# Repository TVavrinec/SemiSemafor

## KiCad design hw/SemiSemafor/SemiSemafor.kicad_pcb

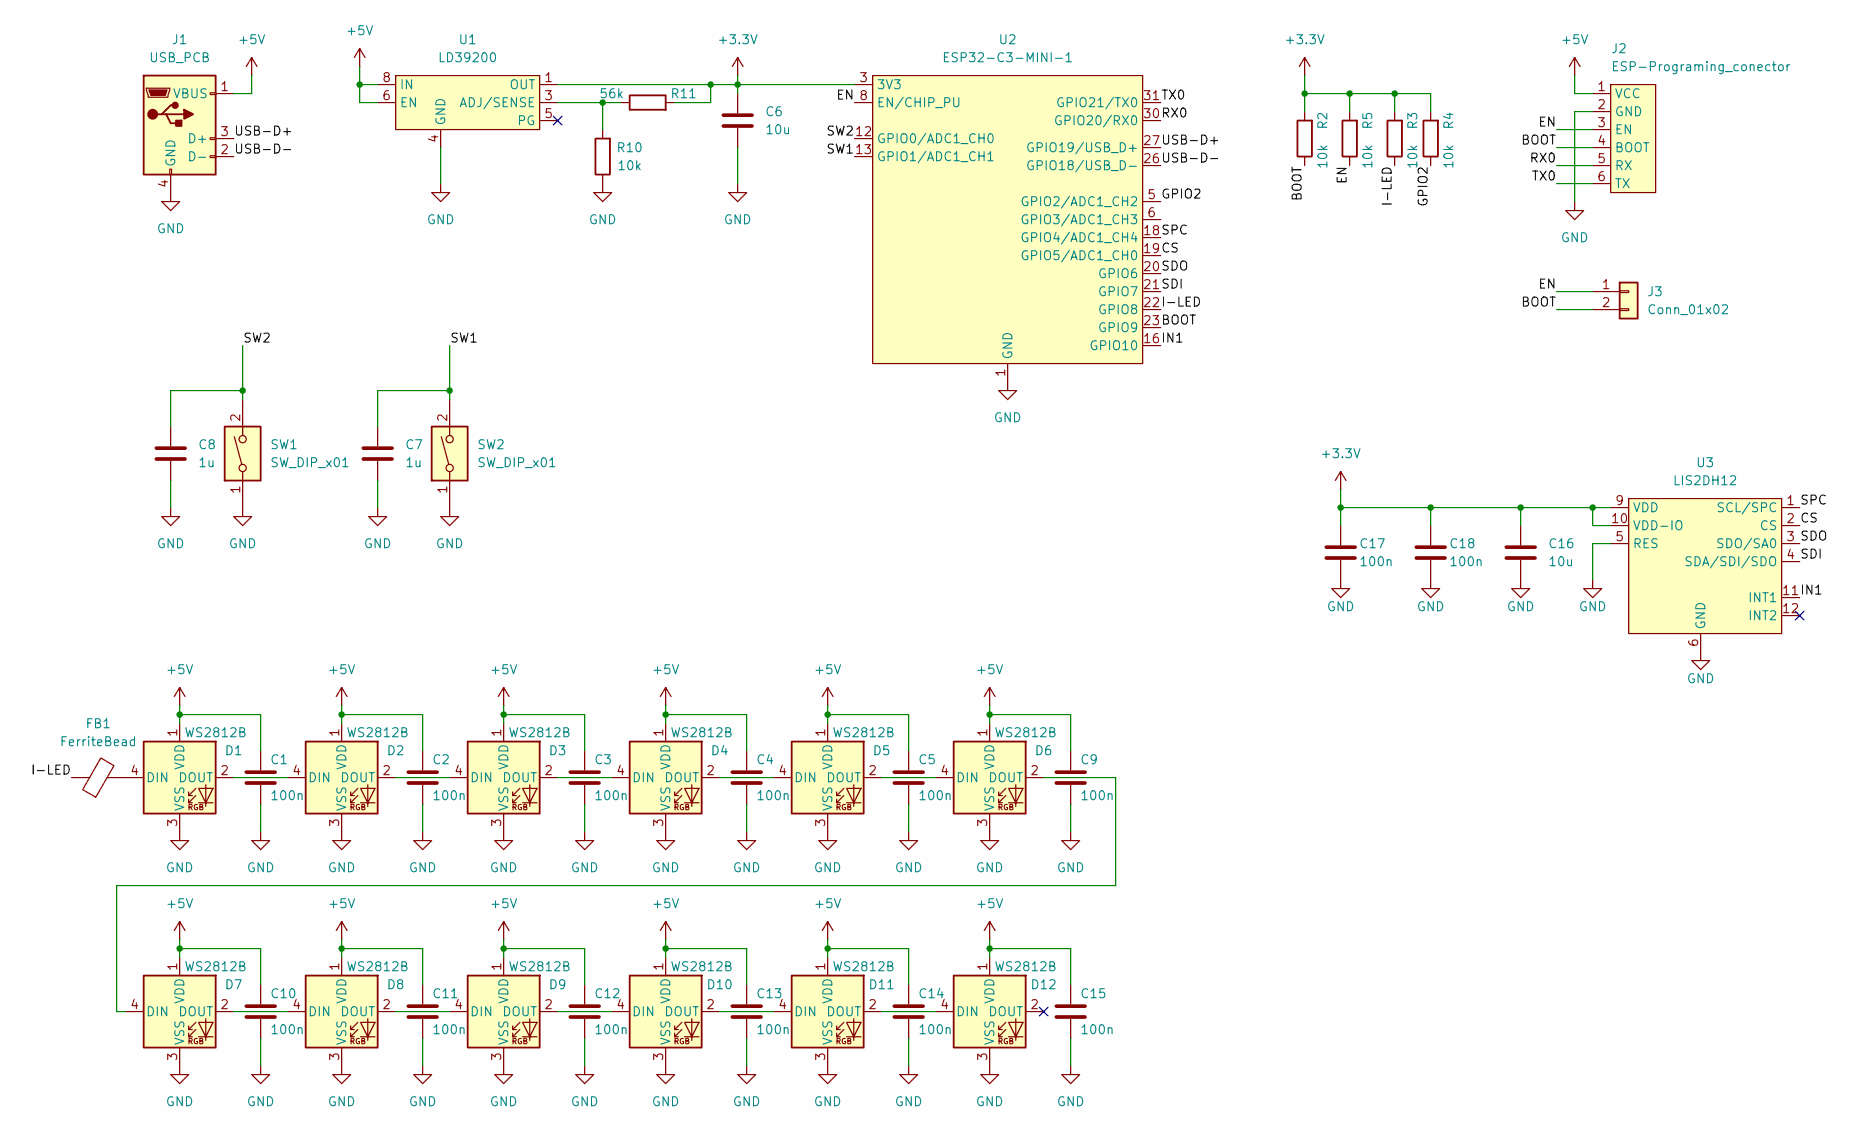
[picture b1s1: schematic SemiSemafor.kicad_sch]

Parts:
C1, C2, C3, C4, C5, C9, C10, C11, C12, C13, C14, C15: 100n; C_0603_1608Metric; LCSC C14663
C6, C16: 10u; C_0603_1608Metric; LCSC C19702
C7, C8: 1u; C_0402_1005Metric; LCSC C52923
C17, C18: 100n; C_0402_1005Metric; LCSC C1525
D1, D2, D3, D4, D5, D6, D7, D8, D9, D10, D11, D12: WS2812B; LED_WS2812B_PLCC4_5.0x5.0mm_P3.2mm; LCSC C2920042
FB1: FerriteBead; L_0402_1005Metric; LCSC C275411
J1: USB_PCB; usb-PCB
J2: ESP-Programing_conector
J3: Conn_01x02; ESP-Small-programming connector
R2, R3, R4, R5, R10: 10k; R_0402_1005Metric; LCSC C25744
R11: 56k; R_0402_1005Metric; LCSC C25796
SW1, SW2: SW_DIP_x01; SW_Push_1P1T_NO_Vertical_Wuerth_434133025816; LCSC C127488
U1: LD39200; DFN-8-1EP_4x4mm_P0.8mm_EP2.3x3.24mm; LCSC C880590
U2: ESP32-C3-MINI-1; LCSC C2838502
U3: LIS2DH12; LGA-12_2x2mm_P0.5mm; LCSC C110926

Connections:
+3.3V: C6.1, C16.1, C17.1, C18.1, R2.2, R3.2, R4.2, R5.2, R11.2, U1.1 (OUT), U1.2 (OUT), U2.3 (3V3), U2.7, U3.9 (VDD), U3.10 (VDD-IO)
+5V: C1.1, C2.1, C3.1, C4.1, C5.1, C9.1, C10.1, C11.1, C12.1, C13.1, C14.1, C15.1, D1.1 (VDD), D2.1 (VDD), D3.1 (VDD), D4.1 (VDD), D5.1 (VDD), D6.1 (VDD), D7.1 (VDD), D8.1 (VDD), D9.1 (VDD), D10.1 (VDD), D11.1 (VDD), D12.1 (VDD), J1.1 (VBUS), J2.1 (VCC), U1.6 (EN), U1.7 (IN), U1.8 (IN)
/BOOT: J2.4 (BOOT), J3.2, R2.1, U2.23 (GPIO9)
/CS: U2.19 (GPIO5/ADC1_CH0), U3.2 (CS)
/EN: J2.3 (EN), J3.1, R5.1, U2.8 (EN/CHIP_PU)
/GPIO2: R4.1, U2.5 (GPIO2/ADC1_CH2)
/I-LED: FB1.1, R3.1, U2.22 (GPIO8)
/IN1: U2.16 (GPIO10), U3.11 (INT1)
/RX0: J2.5 (RX), U2.30 (GPIO20/RX0)
/SDI: U2.21 (GPIO7), U3.4 (SDA/SDI/SDO)
/SDO: U2.20 (GPIO6), U3.3 (SDO/SA0)
/SPC: U2.18 (GPIO4/ADC1_CH4), U3.1 (SCL/SPC)
/SW1: C7.1, SW2.2, U2.13 (GPIO1/ADC1_CH1)
/SW2: C8.1, SW1.2, U2.12 (GPIO0/ADC1_CH0)
/TX0: J2.6 (TX), U2.31 (GPIO21/TX0)
/USB-D+: J1.3 (D+), U2.27 (GPIO19/USB_D+)
/USB-D-: J1.2 (D-), U2.26 (GPIO18/USB_D-)
GND: C1.2, C2.2, C3.2, C4.2, C5.2, C6.2, C7.2, C8.2, C9.2, C10.2, C11.2, C12.2, C13.2, C14.2, C15.2, C16.2, C17.2, C18.2, D1.3 (VSS), D2.3 (VSS), D3.3 (VSS), D4.3 (VSS), D5.3 (VSS), D6.3 (VSS), D7.3 (VSS), D8.3 (VSS), D9.3 (VSS), D10.3 (VSS), D11.3 (VSS), D12.3 (VSS), J1.4 (GND), J2.2 (GND), R10.1, SW1.1, SW2.1, U1.4 (GND), U1.9 (GND), U2.1 (GND), U2.2 (GND), U2.11 (GND), U2.14 (GND), U2.36 (GND), U2.37 (GND), U2.38 (GND), U2.39 (GND), U2.40 (GND), U2.41 (GND), U2.42 (GND), U2.43 (GND), U2.44 (GND), U2.45 (GND), U2.46 (GND), U2.47 (GND), U2.48 (GND), U2.49 (GND), U2.50 (GND), U2.51 (GND), U2.52 (GND), U2.53 (GND), U3.5 (RES), U3.6 (GND), U3.7 (GND), U3.8 (GND)
unnamed: D1.4 (DIN), FB1.2
unnamed: D1.2 (DOUT), D2.4 (DIN)
unnamed: D2.2 (DOUT), D3.4 (DIN)
unnamed: D3.2 (DOUT), D4.4 (DIN)
unnamed: D4.2 (DOUT), D5.4 (DIN)
unnamed: D5.2 (DOUT), D6.4 (DIN)
unnamed: D6.2 (DOUT), D7.4 (DIN)
unnamed: D7.2 (DOUT), D8.4 (DIN)
unnamed: D8.2 (DOUT), D9.4 (DIN)
unnamed: D9.2 (DOUT), D10.4 (DIN)
unnamed: D10.2 (DOUT), D11.4 (DIN)
unnamed: D11.2 (DOUT), D12.4 (DIN)
unnamed: R10.2, R11.1, U1.3 (ADJ/SENSE)

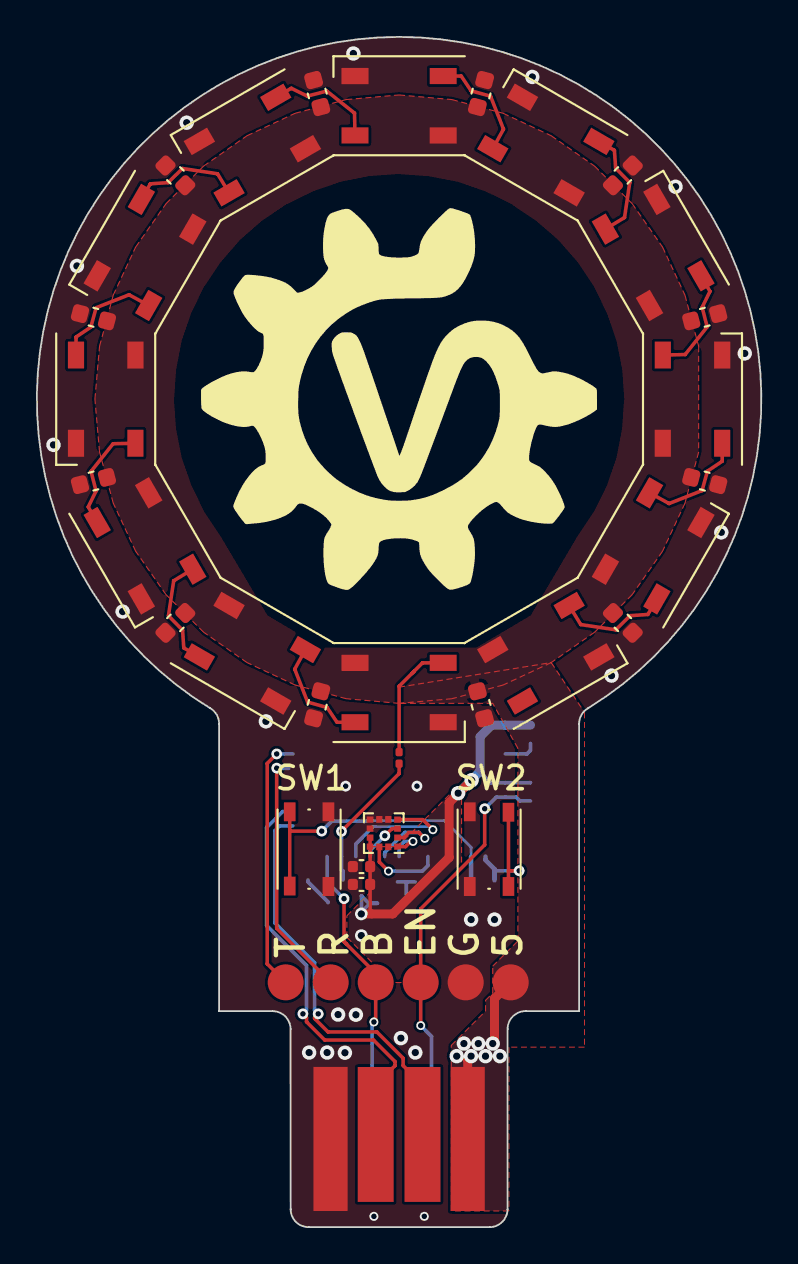
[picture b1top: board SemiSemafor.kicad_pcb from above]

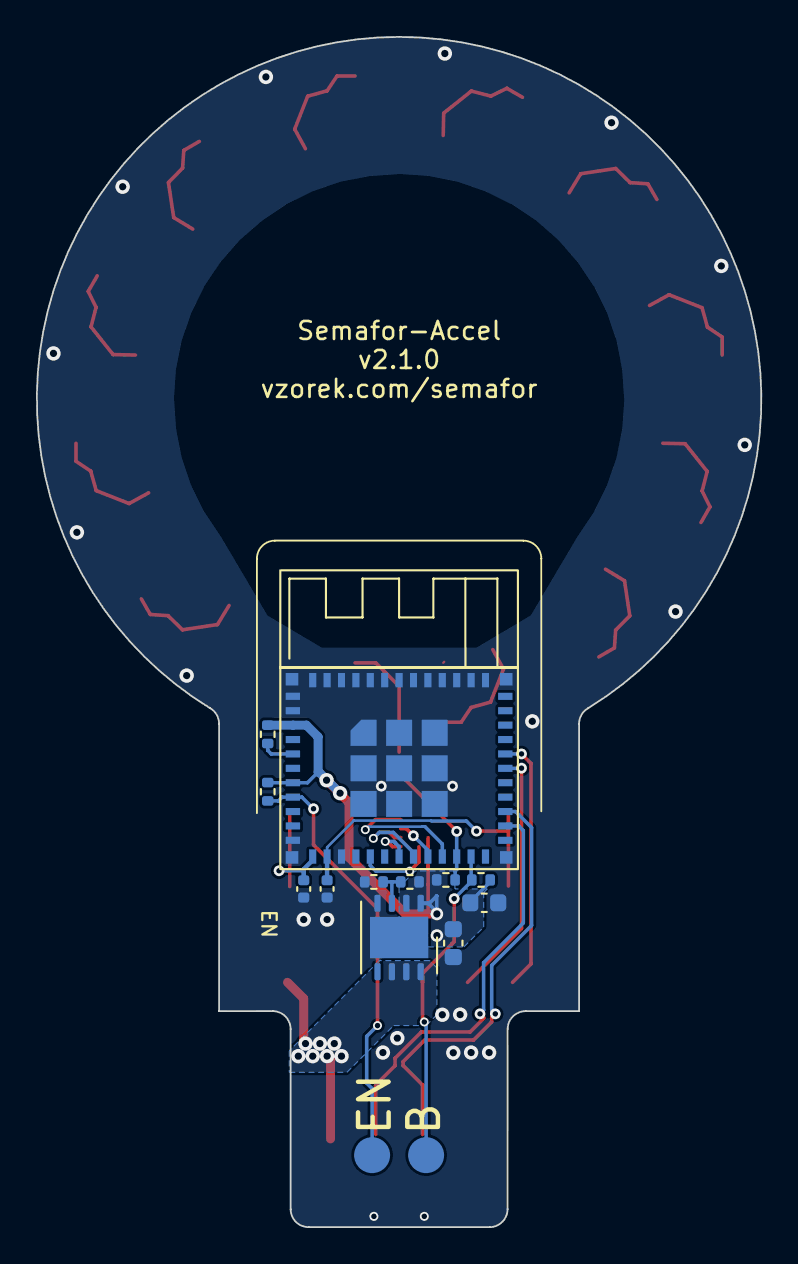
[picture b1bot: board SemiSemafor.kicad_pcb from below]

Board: 2 copper layers, 40.2 x 66.1 mm, 45 parts (13 on the bottom side), 31 nets.

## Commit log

2023-04-03 v1.0
2023-04-06 Change button connection
2023-06-12 fix LDO
2023-08-03 Fix LDO, add button and programming connector
2023-08-06 Polygon and rout tracks correction
2023-08-06 .gitignore
2023-11-25 Add testing code
2023-12-27 gitignore
2024-02-15 12 LED
2024-02-15 V2.0 (Circuit)
2024-02-18 Small ring
2024-02-18 Copper around the hole
2024-02-18 Ring 26mm
2024-02-18 Logo
2024-02-18 SEmafor a SemiSemafor
2024-02-20 Add accelerometer
2024-02-20 Add accelerometer on PCB
2024-02-20 Panel?
2024-02-20 Graphic
2024-02-21 Accelerometer
2024-02-21 5mm LED
2024-02-23 Ferit
2024-03-03 3D-models
2024-04-16 moving the LED circle up
2024-04-21 Add IMU and move LED ring higher
2024-04-26 PCB extension
2024-04-28 Update led count to Semafor
2024-04-28 Add build action
2024-04-28 feat: test imu on semafor
2024-05-04 v2.1.0
2024-05-05 Correction
2024-05-06 Makefile
2024-05-06 Simplified polygons
2024-05-07 Clarity of the makefile
2024-05-07 Change package of FB1
2024-05-23 Solved issue "Micro USB"
2024-06-01 evert "Change package of FB1"
    This reverts commit 3fec99b397d1e8d7d4d9ec397064b3177b82c20d.
    # Conflicts:
    # hw/SemiSemafor/SemiSemafor.kicad_pcb
2024-06-03 feat: show click on leds
2024-06-06 Add print data
2024-06-07 Powerbank holder
2024-06-13 Betr print senings and insert
2024-06-18 placeholder
2024-07-02 3D models
2024-07-02 3D model of insert
2025-07-05 Done
2025-09-08 add king of the hill
